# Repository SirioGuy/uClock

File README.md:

# μClock

**μClock** is a sleek, ultra-precise handheld digital clock — built for makers, engineers, and anyone who values accuracy, simplicity, and reliability.

Powered by the **ESP32-C3**, μClock includes an ultra-precise real-time clock that automatically corrects itself via **NTP servers**, ensuring it's always perfectly on time.

## Features

- ESP32-C3 + 1.3" OLED
- Ultra-low power design
- High-precision clock (±1 PPM)
- NTP sync over Wi-Fi
- Time zone selection
- Open source and customizable

> Work in progress — Hardware revision under validation.

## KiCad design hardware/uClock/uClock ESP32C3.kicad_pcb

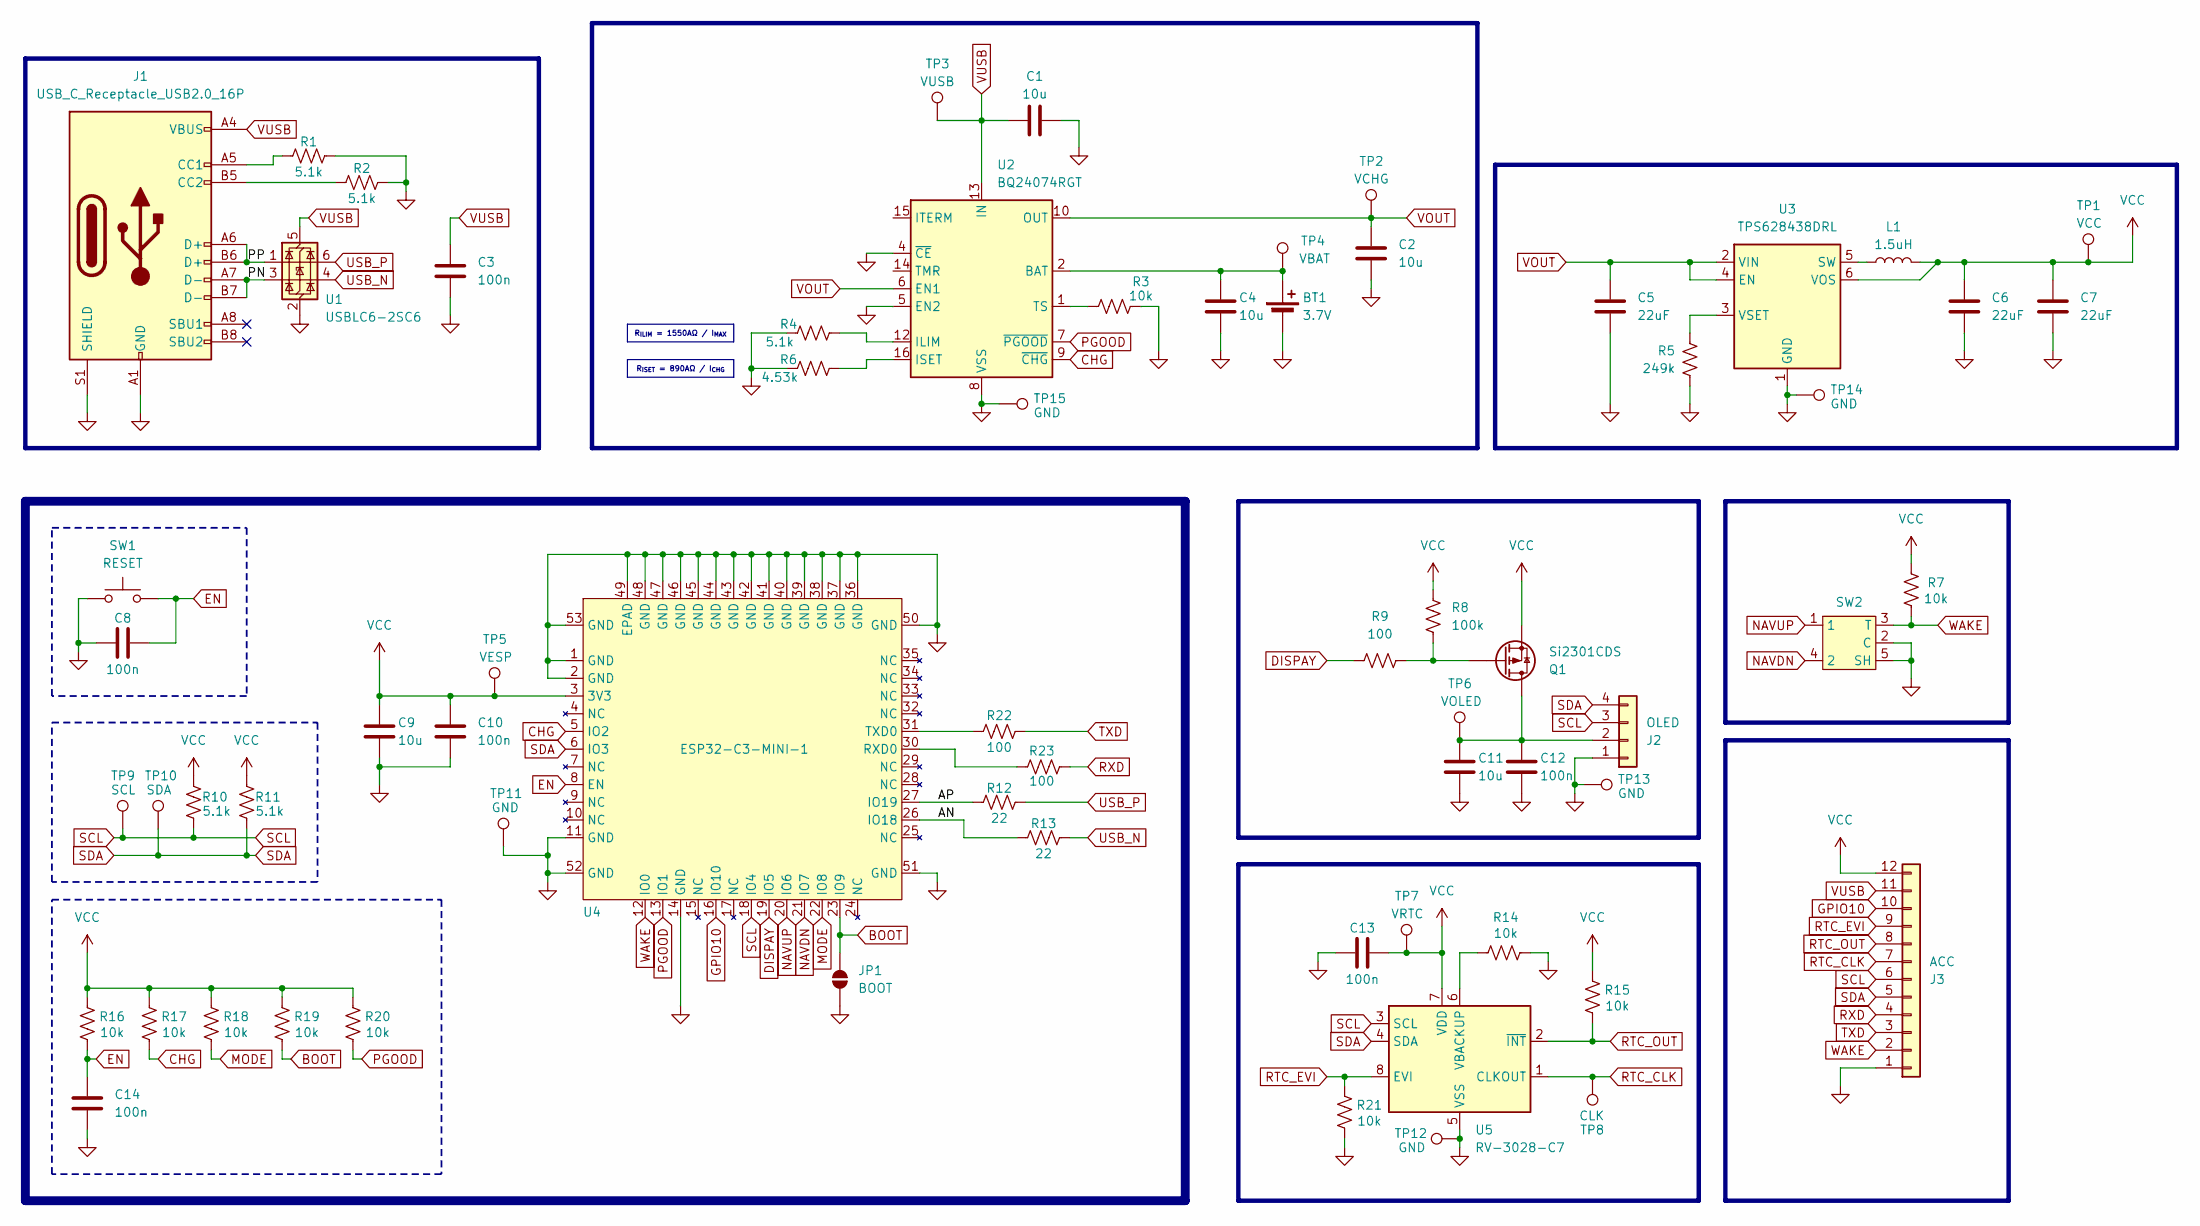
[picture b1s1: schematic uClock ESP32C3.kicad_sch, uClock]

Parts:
BT1: 3.7V; JST-ZH-02AW-P=1.5-H3.6; LCSC C722934
C1, C2, C4, C9, C11: 10u; C_0603_1608Metric; LCSC C19702
C3, C8, C10, C12, C13, C14: 100n; C_0603_1608Metric; LCSC C14663
C5, C6, C7: 22uF; C_0805_2012Metric; LCSC C907991
J1: USB_C_Receptacle_USB2.0_16P; USB_C_Receptacle_GCT_USB4105-xx-A_16P_TopMnt_Horizontal; LCSC C2765186
J2: OLED; PinSocket_1x04_P2.54mm_Vertical
J3: ACC; PinHeader_1x12_P1.27mm_Vertical
JP1: BOOT; SolderJumper-2_P1.3mm_Open_RoundedPad1.0x1.5mm
L1: 1.5uH; L_0806; LCSC C3020027
Q1: Si2301CDS; TSOT-23; LCSC C10487
R1, R2, R4, R10, R11: 5.1k; R_0603_1608Metric; LCSC C23186
R3, R7, R14, R15, R16, R17, R18, R19, R20, R21: 10k; R_0603_1608Metric; LCSC C25804
R5: 249k; R_0603_1608Metric; LCSC C22918
R6: 4.53k; R_0603_1608Metric; LCSC C25971
R8: 100k; R_0603_1608Metric; LCSC C25803
R9, R22, R23: 100; R_0603_1608Metric; LCSC C22775
R12, R13: 22; R_0603_1608Metric; LCSC C23345
SW1: RESET; SW_SPST_TS-1088-xR020; LCSC C720477
SW2: K1-1511SA-01; LCSC C145907
TP1: VCC; TestPoint_Pad_D1.0mm
TP2: VCHG; TestPoint_Pad_D1.0mm
TP3: VUSB; TestPoint_Pad_D1.0mm
TP4: VBAT; TestPoint_Pad_D1.0mm
TP5: VESP; TestPoint_Pad_D1.0mm
TP6: VOLED; TestPoint_Pad_D1.0mm
TP7: VRTC; TestPoint_Pad_D1.0mm
TP8: CLK; TestPoint_Pad_D1.0mm
TP9: SCL; TestPoint_Pad_D1.0mm
TP10: SDA; TestPoint_Pad_D1.0mm
TP11, TP12, TP13, TP14, TP15: GND; TestPoint_Pad_D1.0mm
U1: USBLC6-2SC6; SOT-23-6; LCSC C7519
U2: BQ24074RGT; VQFN-16-1EP_3x3mm_P0.5mm_EP1.6x1.6mm_ThermalVias; LCSC C54313
U3: TPS628438DRL; SOT-563; LCSC C38060243
U4: ESP32-C3-MINI-1; LCSC C2934569
U5: RV-3028-C7; MicroCrystal_C7_SON-8_1.5x3.2mm_P0.9mm; LCSC C3019759

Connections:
/AN: R13.1, U4.26 (IO18)
/AP: R12.1, U4.27 (IO19)
/PN: J1.A7 (D-), J1.B7 (D-), U1.3 (I/O2)
/PP: J1.A6 (D+), J1.B6 (D+), U1.1 (I/O1)
BOOT: JP1.2 (B), R19.2, U4.23 (IO9)
CHG: R17.2, U2.9 (~CHG), U4.5 (IO2)
DISPAY: R9.1, U4.19 (IO5)
EN: C8.2, C14.1, R16.2, SW1.2, U4.8 (EN)
GND: BT1.2 (-), C1.2, C2.2, C3.2, C4.2, C5.2, C6.2, C7.2, C8.1, C9.2, C10.2, C11.2, C12.2, C13.1, C14.2, J1.A1 (GND), J1.A12 (GND), J1.B1 (GND), J1.B12 (GND), J1.S1 (SHIELD), J2.1, J3.1, JP1.1 (A), R1.2, R2.2, R3.2, R4.1, R5.2, R6.1, R14.2, R21.2, SW1.1, SW2.2 (C), SW2.5 (SH), TP11.1, TP12.1, TP13.1, TP14.1, TP15.1, U1.2 (GND), U2.4 (~CE), U2.5 (EN2), U2.8 (VSS), U2.17 (VSS), U3.1 (GND), U4.1 (GND), U4.2 (GND), U4.11 (GND), U4.14 (GND), U4.36 (GND), U4.37 (GND), U4.38 (GND), U4.39 (GND), U4.40 (GND), U4.41 (GND), U4.42 (GND), U4.43 (GND), U4.44 (GND), U4.45 (GND), U4.46 (GND), U4.47 (GND), U4.48 (GND), U4.49 (EPAD), U4.50 (GND), U4.51 (GND), U4.52 (GND), U4.53 (GND), U5.5 (VSS)
GPIO10: J3.10, U4.16 (IO10)
MODE: R18.2, U4.22 (IO8)
NAVDN: SW2.4 (2), U4.21 (IO7)
NAVUP: SW2.1, U4.20 (IO6)
unnamed: BT1.1 (+), C4.1, TP4.1, U2.2 (BAT), U2.3 (BAT)
unnamed: J1.A5 (CC1), R1.1
unnamed: J1.B5 (CC2), R2.1
unnamed: C11.1, C12.1, J2.2, Q1.3 (D), TP6.1
unnamed: Q1.1 (G), R8.2, R9.2
unnamed: R4.2, U2.12 (ILIM)
unnamed: R6.2, U2.16 (ISET)
unnamed: R3.1, U2.1 (TS)
unnamed: L1.1, U3.5 (SW)
unnamed: R5.1, U3.3 (VSET)
unnamed: R23.1, U4.30 (RXD0)
unnamed: R22.1, U4.31 (TXD0)
unnamed: R14.1, U5.6 (VBACKUP)
PGOOD: R20.2, U2.7 (~PGOOD), U4.13 (IO1)
RTC_CLK: J3.7, TP8.1, U5.1 (CLKOUT)
RTC_EVI: J3.9, R21.1, U5.8 (EVI)
RTC_OUT: J3.8, R15.2, U5.2 (~INT)
RXD: J3.4, R23.2
SCL: J2.3, J3.6, R10.1, TP9.1, U4.18 (IO4), U5.3 (SCL)
SDA: J2.4, J3.5, R11.1, TP10.1, U4.6 (IO3), U5.4 (SDA)
TXD: J3.3, R22.2
USB_N: R13.2, U1.4 (I/O2)
USB_P: R12.2, U1.6 (I/O1)
VCC: C6.1, C7.1, C9.1, C10.1, C13.2, J3.12, L1.2, Q1.2 (S), R7.1, R8.1, R10.2, R11.2, R15.1, R16.1, R17.1, R18.1, R19.1, R20.1, TP1.1, TP5.1, TP7.1, U3.6 (VOS), U4.3 (3V3), U5.7 (VDD)
VOUT: C2.1, C5.1, TP2.1, U2.6 (EN1), U2.10 (OUT), U2.11 (OUT), U3.2 (VIN), U3.4 (EN)
VUSB: C1.1, C3.1, J1.A4 (VBUS), J1.A9 (VBUS), J1.B4 (VBUS), J1.B9 (VBUS), J3.11, TP3.1, U1.5 (VBUS), U2.13 (IN)
WAKE: J3.2, R7.2, SW2.3 (T), U4.12 (IO0)

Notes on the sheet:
R_{ILIM} = 1550AΩ / I_{MAX}
R_{ISET} = 890AΩ / I_{CHG}

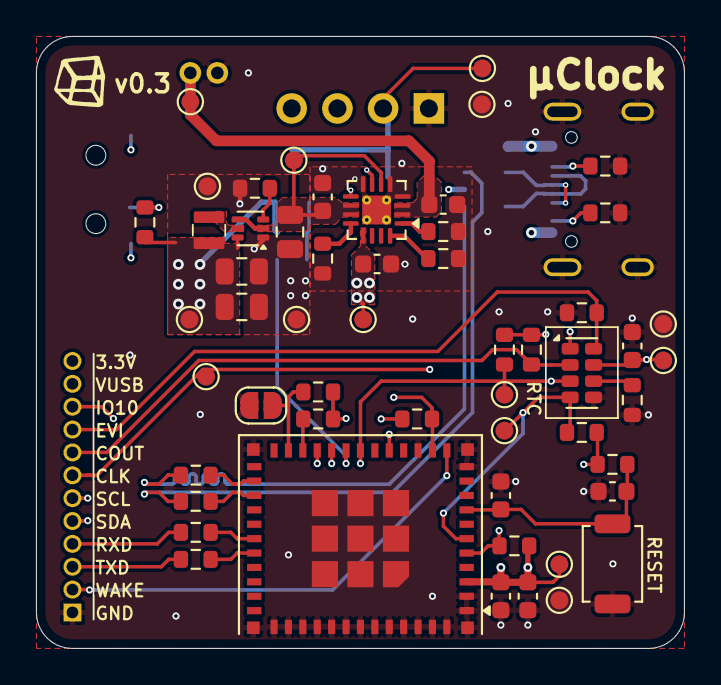
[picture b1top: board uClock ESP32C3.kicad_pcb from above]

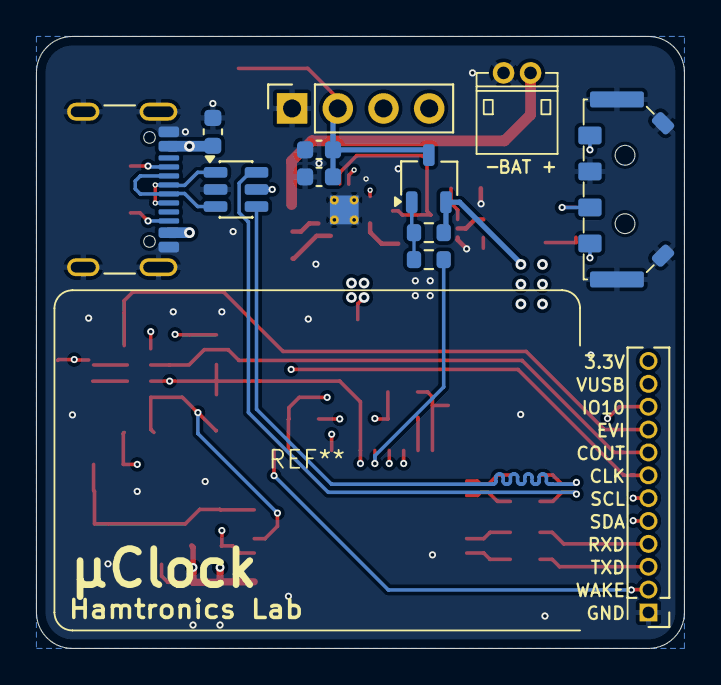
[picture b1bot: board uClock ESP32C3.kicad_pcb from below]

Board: 4 copper layers, 36.0 x 34.0 mm, 66 parts (12 on the bottom side), 40 nets.

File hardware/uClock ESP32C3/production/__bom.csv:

Designator,Footprint,Quantity,Value,LCSC Part #
BT1,JST-ZH-02AW-P=1.5-H3.6,1,3.7V,C722934
"C1, C11, C2, C4, C9",0603,5,10u,C19702
"C10, C12, C13, C14, C3, C8",0603,6,100n,C14663
"C5, C6, C7",0805,3,22uF,C907991
J1,USB_C_Receptacle_GCT_USB4105-xx-A_16P_TopMnt_Horizontal,1,USB_C_Receptacle_USB2.0_16P,C2765186
L1,L_0806,1,1.5uH,C3020027
Q1,TSOT-23,1,Si2301CDS,C10487
"R1, R10, R11, R2, R4",0603,5,5.1k,C23186
"R12, R13",0603,2,22,C23345
"R14, R15, R16, R17, R18, R19, R20, R21, R3, R7",0603,10,10k,C25804
"R22, R23, R9",0603,3,100,C22775
R5,0603,1,249k,C22918
R6,0603,1,4.53k,C25971
R8,0603,1,100k,C25803
SW1,SW_SPST_TS-1088-xR020,1,RESET,C720477
SW2,K1-1511SA-01,1,~,C145907
U1,SOT-23-6,1,USBLC6-2SC6,C7519
U2,VQFN-16-1EP_3x3mm_P0.5mm_EP1.6x1.6mm_ThermalVias,1,BQ24074RGT,C54313
U3,SOT-563,1,TPS628438DRL,C38060243
U4,ESP32-C3-MINI-1,1,ESP32-C3-MINI-1,C2934569
U5,MicroCrystal_C7_SON-8_1.5x3.2mm_P0.9mm,1,RV-3028-C7,

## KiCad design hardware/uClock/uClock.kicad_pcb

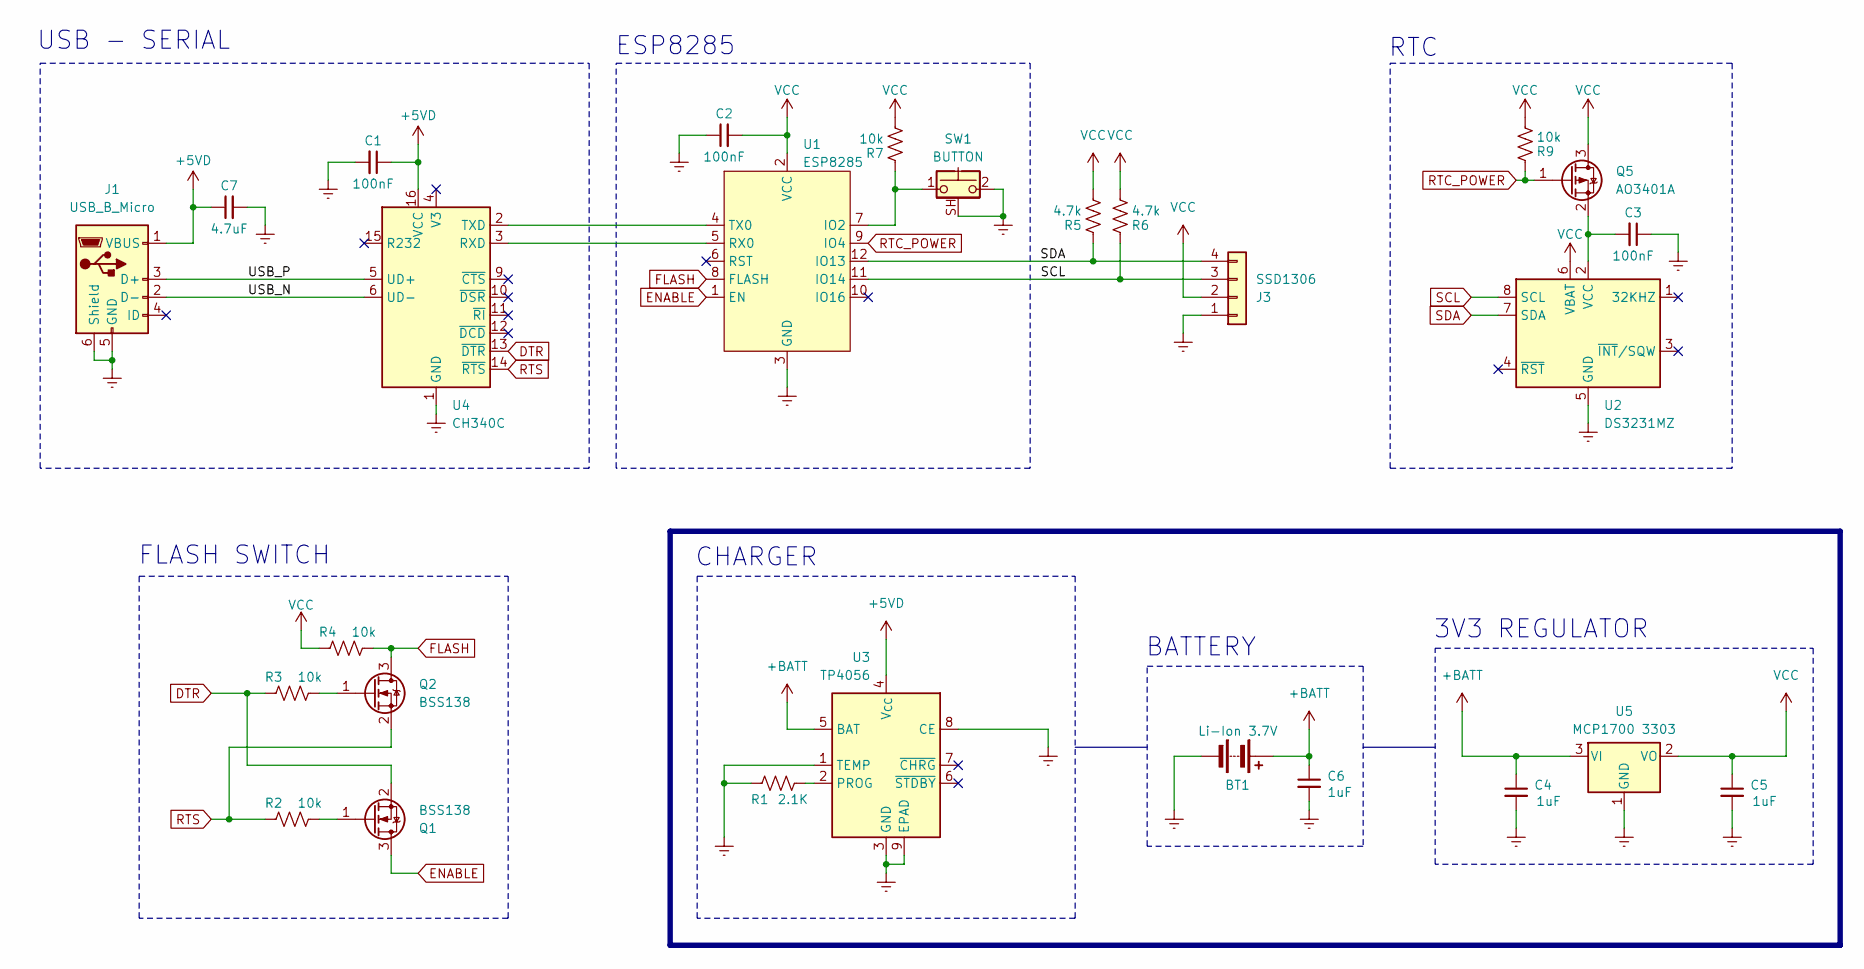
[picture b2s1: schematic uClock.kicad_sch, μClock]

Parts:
BT1: Li-Ion 3.7V; JST_PH_B2B-PH-K_1x02_P2.00mm_Vertical
C1, C2, C3: 100nF; C_0603_1608Metric_Pad1.08x0.95mm_HandSolder
C4, C5, C6: 1uF; C_0603_1608Metric_Pad1.08x0.95mm_HandSolder
C7: 4.7uF; C_0603_1608Metric_Pad1.08x0.95mm_HandSolder
J1: USB_B_Micro; USB_Micro-B_Amphenol_10104110_Horizontal
J3: SSD1306; PinSocket_1x04_P2.54mm_Vertical
Q1, Q2: BSS138; SOT-23
Q5: AO3401A; SOT-23
R1: 2.1K; R_0603_1608Metric_Pad0.98x0.95mm_HandSolder
R2, R3, R4, R7, R9: 10k; R_0603_1608Metric_Pad0.98x0.95mm_HandSolder
R5, R6: 4.7k; R_0603_1608Metric_Pad0.98x0.95mm_HandSolder
SW1: BUTTON; SW_PUSH_ANGLED_SMD
U1: ESP8285; ESP8285 ESP-M3 MODULE
U2: DS3231MZ; SOIC-8_3.9x4.9mm_P1.27mm
U3: TP4056; SOIC-8-1EP_3.9x4.9mm_P1.27mm_EP2.29x3mm
U4: CH340C; SOIC-16_3.9x9.9mm_P1.27mm
U5: MCP1700 3303; SOT-23

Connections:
+5VD: C1.1, C7.1, J1.1 (VBUS), U3.4 (V_{CC}), U4.16 (VCC)
+BATT: BT1.1 (+), C4.1, C6.1, U3.5 (BAT), U5.3 (VI)
/USB_N: J1.2 (D-), U4.6 (UD-)
/USB_P: J1.3 (D+), U4.5 (UD+)
DTR: Q1.2 (S), R3.1, U4.13 (~DTR)
ENABLE: Q1.3 (D), U1.1 (EN)
Earth: BT1.2 (-), C1.2, C2.1, C3.1, C4.2, C5.2, C6.2, C7.2, J1.5 (GND), J1.6 (Shield), J3.1, R1.1, SW1.2, SW1.SH (B), U1.3 (GND), U2.5 (GND), U3.1 (TEMP), U3.3 (GND), U3.8 (CE), U3.9 (EPAD), U4.1 (GND), U5.1 (GND)
FLASH: Q2.3 (D), R4.2, U1.8 (FLASH)
unnamed: Q1.1 (G), R2.2
unnamed: Q2.1 (G), R3.2
unnamed: C3.2, Q5.2 (S), U2.2 (VCC)
unnamed: R7.1, SW1.1, U1.7 (IO2)
unnamed: U1.5 (RX0), U4.3 (RXD)
unnamed: U1.4 (TX0), U4.2 (TXD)
unnamed: R1.2, U3.2 (PROG)
RTC_POWER: Q5.1 (G), R9.1, U1.9 (IO4)
RTS: Q2.2 (S), R2.1, U4.14 (~RTS)
SCL: J3.3, R6.1, U1.11 (IO14), U2.8 (SCL)
SDA: J3.4, R5.1, U1.12 (IO13), U2.7 (SDA)
VCC: C2.2, C5.1, J3.2, Q5.3 (D), R4.1, R5.2, R6.2, R7.2, R9.2, U1.2 (VCC), U2.6 (VBAT), U5.2 (VO)

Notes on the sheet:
CHARGER
USB - SERIAL
RTC
ESP8285
3V3 REGULATOR
BATTERY
FLASH SWITCH

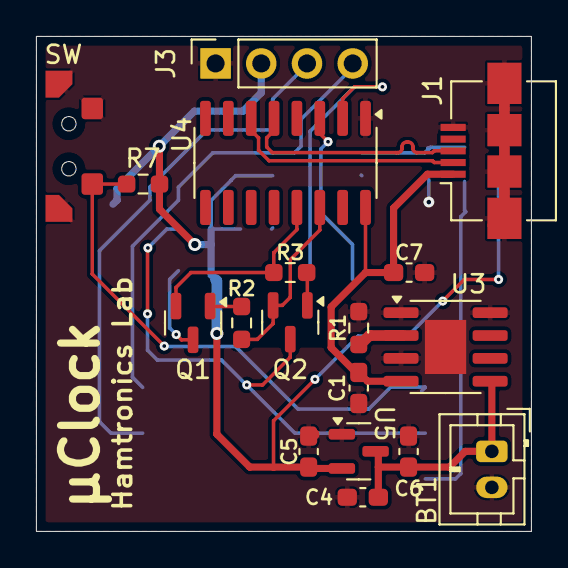
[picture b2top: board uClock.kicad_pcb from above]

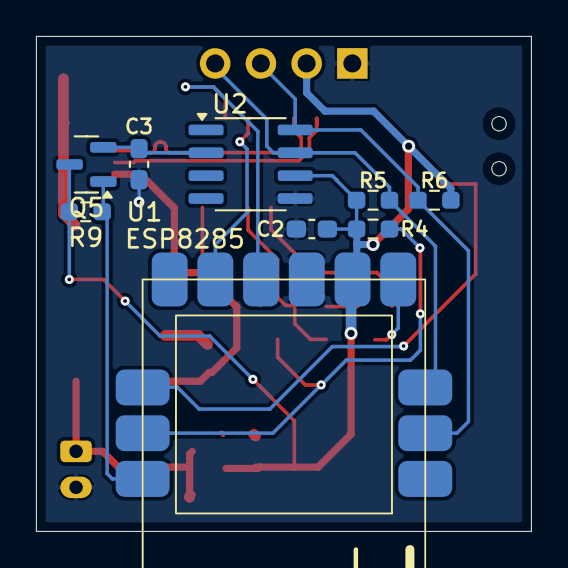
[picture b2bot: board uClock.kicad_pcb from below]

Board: 2 copper layers, 27.5 x 27.5 mm, 27 parts (9 on the bottom side), 20 nets.

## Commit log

2025-06-17 3d models
2025-06-17 Update folders
2025-06-17 Update kicad files
2025-06-17 deleted innecesary files
2025-06-17 Added firmware tests
2025-06-18 PCB Update - rev2
    - CH340 power corrected
    - Optimized RTC conspumtion
    - Pullup added to SW1
2025-06-21 Updated PCB to REV-3
    - Updated PCB traces tolerances from 0.3mm to 0.2mm
    - Optimized some traces
2025-06-25 name update
2026-02-21 ESP32C3 Ver 0.3 Rev 1
2026-02-22 README update
2026-02-23 Update Ver 0.3 REV 1
